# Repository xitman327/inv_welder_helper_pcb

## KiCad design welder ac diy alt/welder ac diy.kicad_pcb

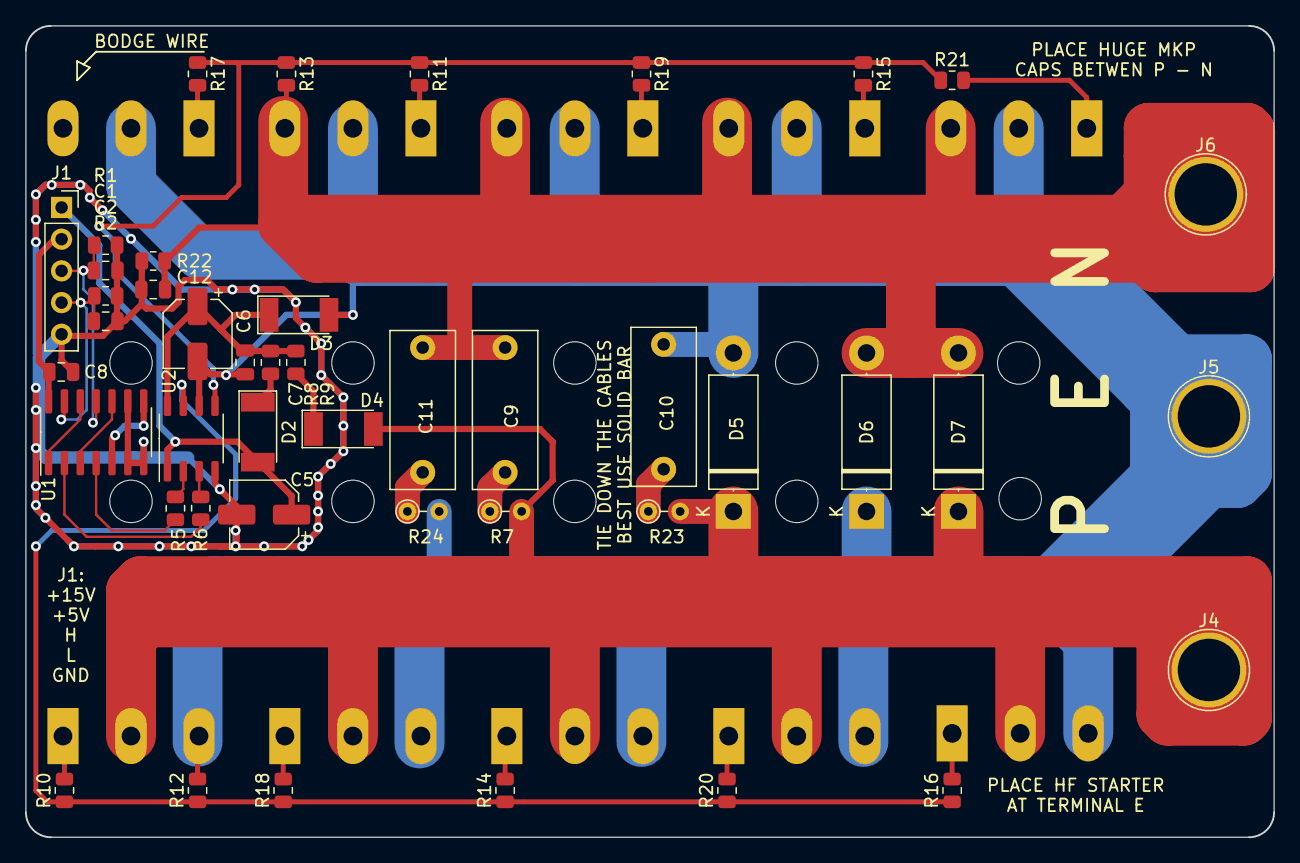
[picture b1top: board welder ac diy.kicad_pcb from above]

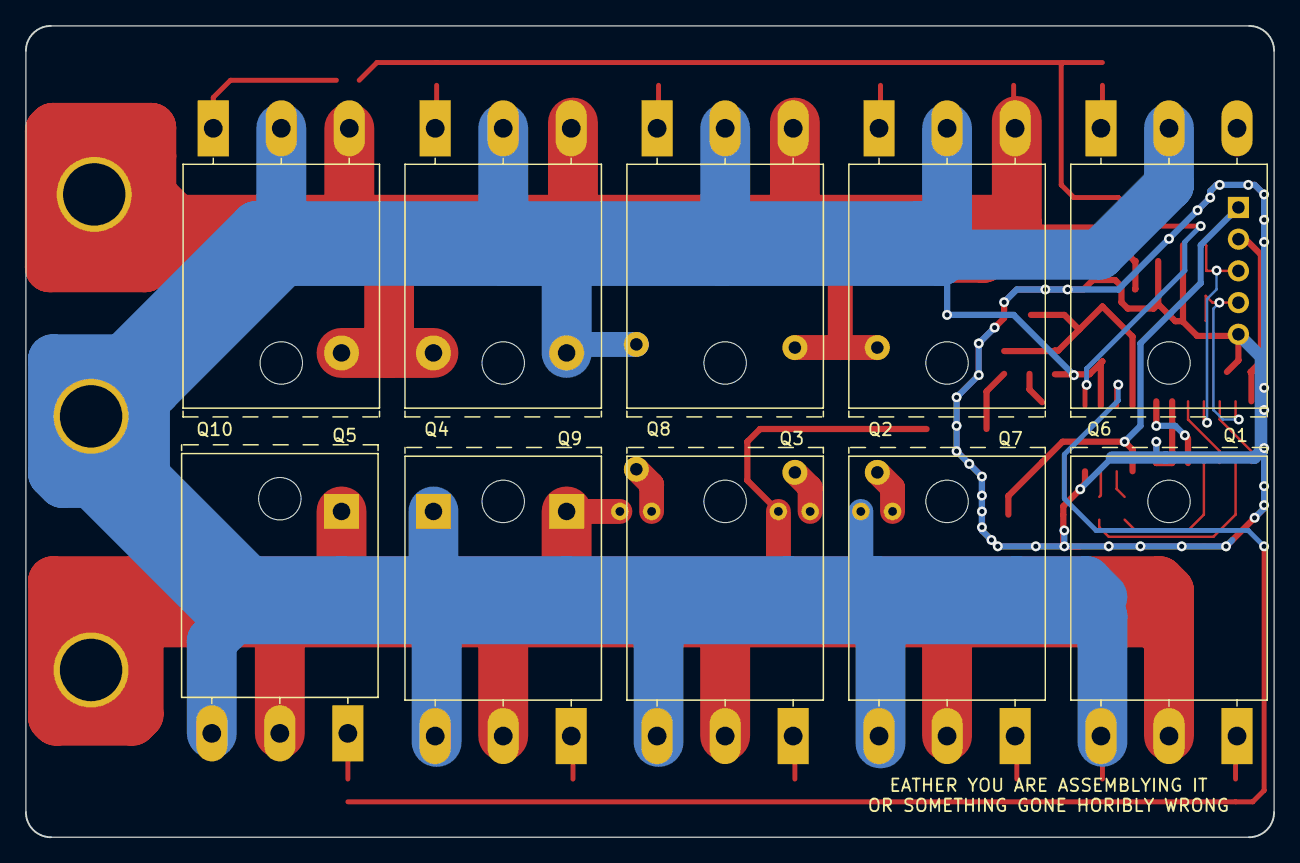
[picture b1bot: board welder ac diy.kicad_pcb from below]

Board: 2 copper layers, 100.0 x 65.0 mm, 54 parts (10 on the bottom side), 33 nets.

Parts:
C1, C2, C7, C8, C12: C_Small; C_0805_2012Metric
C5, C6: C_Polarized_Small; CP_Elec_5x5.7
C9, C10, C11: C_Small; C_Disc_D12.5mm_W5.0mm_P10.00mm
D2, D3, D4: D_Small; D_MELF
D5, D6, D7: D_Small; D_5W_P12.70mm_Horizontal
J1: Conn_01x05; PinSocket_1x05_P2.54mm_Vertical
J4, J5, J6: Conn_01x01; TestPoint_Plated_Hole_D5.0mm
Q1, Q2, Q3, Q4, Q5, Q6, Q7, Q8, Q9, Q10: Q_NMOS_GDS; TO-3P-3_Horizontal_TabUp
R1, R2, R5, R6, R8, R9, R10, R11, R12, R13, R14, R15, R16, R17, R18, R19, R20, R21, R22: R_Small; R_0805_2012Metric
R7, R23, R24: R_Small; R_Axial_DIN0204_L3.6mm_D1.6mm_P2.54mm_Vertical
U1: 74HC04; SO-14_3.9x8.65mm_P1.27mm
U2: IR2101; SOP-8_3.9x4.9mm_P1.27mm

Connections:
+5V: C8.1, J1.2, U1.14 (VCC)
+15V: C5.1, D2.2 (A), J1.1, U2.1 (VCC)
/in+: D4.2 (A), D5.1 (K), D7.1 (K), J4.1, Q1.2 (D), Q3.2 (D), Q5.2 (D), Q7.2 (D), Q9.2 (D), R7.2, R23.2
/in-: C9.2, C11.2, C12.2, D6.2 (A), D7.2 (A), J6.1, Q2.3 (S), Q4.3 (S), Q6.3 (S), Q8.3 (S), Q10.3 (S), R13.2, R22.2
/outP: C6.2, C7.2, C10.2, D3.2 (A), D5.2 (A), D6.1 (K), J5.1, Q1.3 (S), Q2.2 (D), Q3.3 (S), Q4.2 (D), Q5.3 (S), Q6.2 (D), Q7.3 (S), Q8.2 (D), Q9.3 (S), Q10.2 (D), R12.2, R24.2, U2.6 (VS)
GND: C1.2, C2.2, C5.2, C8.2, C12.1, J1.5, R1.1, R2.1, R22.1, U1.6, U1.7 (GND), U1.9, U2.4 (COM)
unnamed: C9.1, R7.1
unnamed: C10.1, R23.1
unnamed: C11.1, R24.1
unnamed: D2.1 (K), R8.1
unnamed: C6.1, C7.1, D3.1 (K), R8.2, R9.1, U2.8 (VB)
unnamed: D4.1 (K), R9.2
unnamed: C1.1, J1.3, R1.2, U1.11
unnamed: C2.1, J1.4, R2.2, U1.13
unnamed: Q1.1 (G), R10.2
unnamed: Q2.1 (G), R11.2
unnamed: Q3.1 (G), R14.2
unnamed: Q4.1 (G), R15.2
unnamed: Q5.1 (G), R16.2
unnamed: Q6.1 (G), R17.2
unnamed: Q7.1 (G), R18.2
unnamed: Q8.1 (G), R19.2
unnamed: Q9.1 (G), R20.2
unnamed: Q10.1 (G), R21.2
unnamed: R5.1, U1.4
unnamed: R6.1, U1.2
unnamed: U1.1, U1.12
unnamed: U1.3, U1.10
unnamed: U1.5, U1.8
unnamed: R5.2, U2.2 (HIN)
unnamed: R10.1, R12.1, R14.1, R16.1, R18.1, R20.1, U2.7 (HO)
unnamed: R6.2, U2.3 (LIN)
unnamed: R11.1, R13.1, R15.1, R17.1, R19.1, R21.1, U2.5 (LO)

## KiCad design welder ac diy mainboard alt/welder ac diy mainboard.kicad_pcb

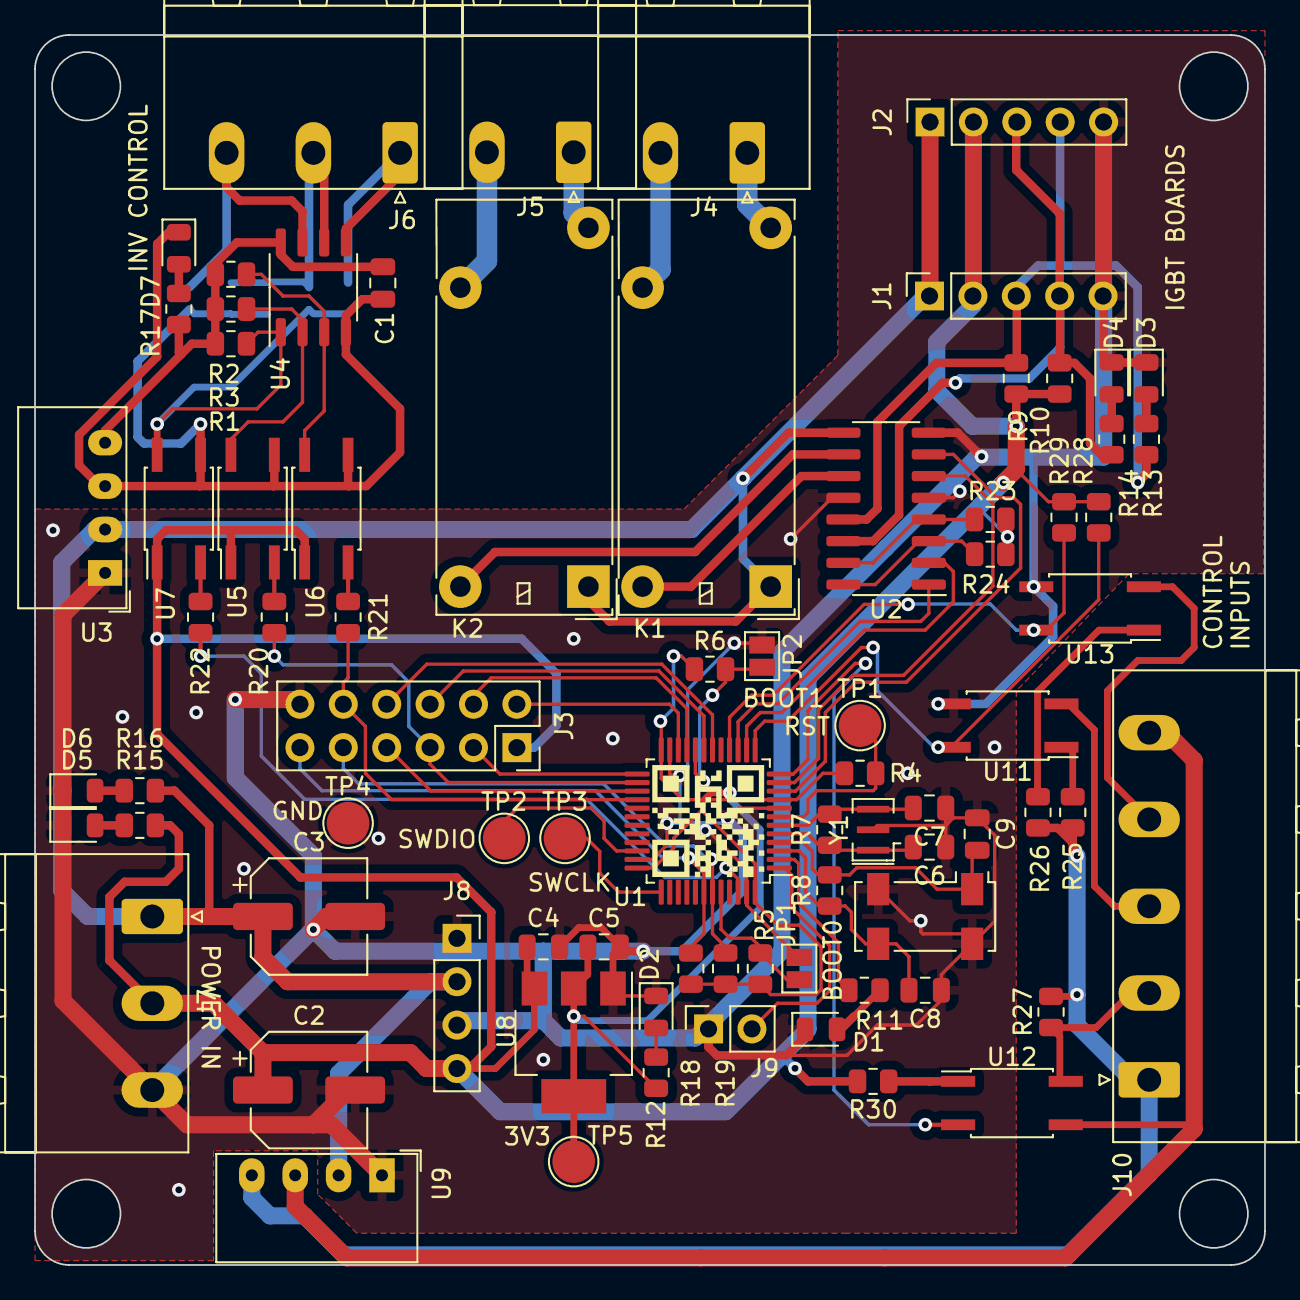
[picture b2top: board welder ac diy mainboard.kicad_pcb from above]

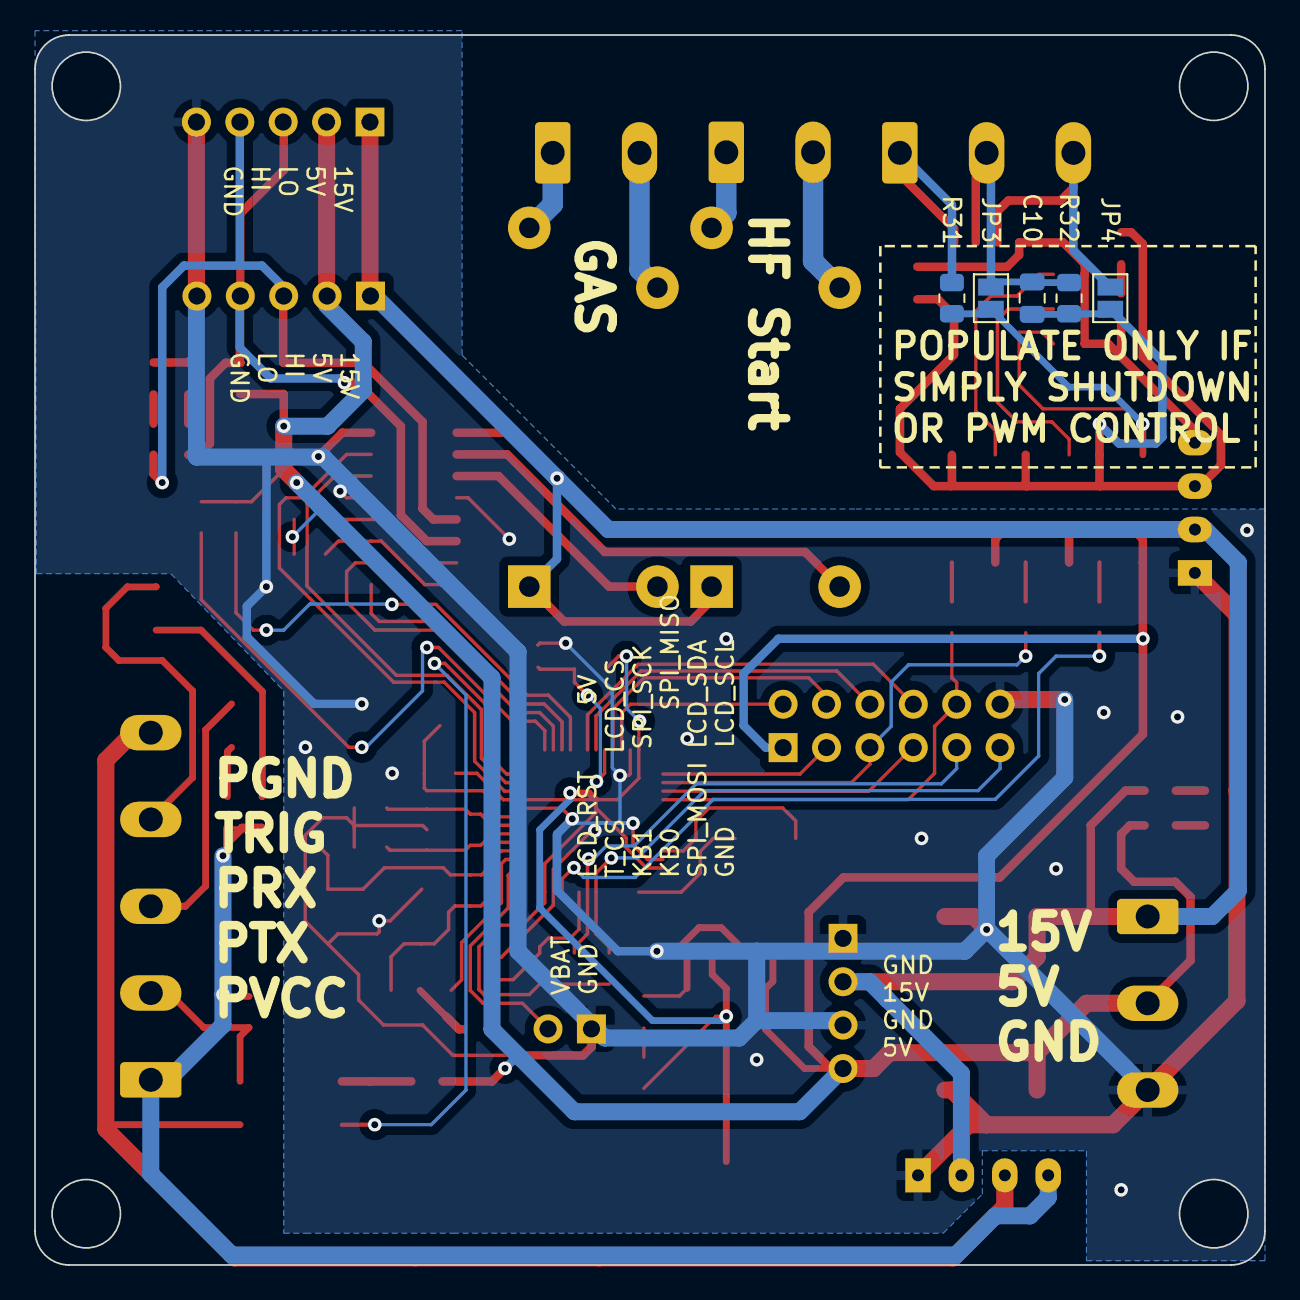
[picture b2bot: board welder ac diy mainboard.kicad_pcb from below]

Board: 2 copper layers, 72.0 x 72.0 mm, 84 parts (5 on the bottom side), 69 nets.

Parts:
C1, C4, C5, C6, C7, C8, C9, C10: C_Small; C_0805_2012Metric
C2, C3: C_Polarized_Small; CP_Elec_6.3x3
D1, D2, D3, D4, D5, D6, D7: LED; LED_0805_2012Metric
J1, J2: Conn_01x05; PinSocket_1x05_P2.54mm_Vertical
J3: Conn_02x06_Odd_Even; PinSocket_2x06_P2.54mm_Vertical
J4, J5: Conn_01x02; PhoenixContact_MSTBA_2,5_2-G-5,08_1x02_P5.08mm_Horizontal
J6, J7: Conn_01x03; PhoenixContact_MSTBA_2,5_3-G-5,08_1x03_P5.08mm_Horizontal
J8: Conn_01x04; PinSocket_1x04_P2.54mm_Vertical
J9: Conn_01x02; PinSocket_1x02_P2.54mm_Vertical
J10: Conn_01x05; PhoenixContact_MSTBA_2,5_5-G-5,08_1x05_P5.08mm_Horizontal
JP1, JP2, JP3, JP4: SolderJumper_2_Open; SolderJumper-2_P1.3mm_Open_Pad1.0x1.5mm
K1, K2: ADW11; Relay_1P1T_NO_10x24x18.8mm_Panasonic_ADW11xxxxW_THT
R1, R2, R3, R4, R5, R6, R7, R8, R9, R10, R11, R12, R13, R14, R15, R16, R17, R18, R19, R20, R21, R22, R23, R24, R25, R26, R27, R28, R29, R30, R31, R32: R_Small; R_0805_2012Metric
TP1, TP2, TP3, TP4, TP5: TestPoint; TestPoint_Pad_D2.5mm
U1: STM32F103C8Tx; LQFP-48_7x7mm_P0.5mm
U2: ULN2003; SOP-16_3.9x9.9mm_P1.27mm
U3, U9: CRE1S0515SC; Converter_DCDC_Murata_CRE1xxxxxxSC_THT
U4: MCP41010; SOP-8_3.9x4.9mm_P1.27mm
U5, U6, U7, U11, U12, U13: LTV-357T; SO-4_4.4x3.6mm_P2.54mm
U8: AMS1117-2.85; SOT-223-3_TabPin2
Y1: Crystal_GND2_Small; Resonator_SMD_Murata_CSTxExxV-3Pin_3.0x1.1mm
Y3: Crystal_GND24_Small; Crystal_SMD_Abracon_ABS25-4Pin_8.0x3.8mm

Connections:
+5V: C2.1, C4.1, J1.2, J2.2, J3.1, J7.2, J8.4, R9.1, R10.1, R15.1, R23.1, R24.1, R28.2, R29.2, R30.2, U5.1, U6.1, U7.1, U8.3 (VI)
+15V: C3.1, J1.1, J2.1, J7.1, J8.2, K1.1, K2.1, R16.1, U2.9 (COM), U3.2 (+VIN), U9.2 (+VIN)
/CLK1: R24.2, U2.3 (I3), U2.16 (O1)
/CLK2: J1.4, J2.3, R10.2, R14.1, U2.14 (O3)
/CLK_: U1.15 (PA5), U2.1 (I1)
/EN1: R23.2, U2.4 (I4), U2.15 (O2)
/EN2: J1.3, J2.4, R9.2, R13.1, U2.13 (O4)
/EN_: U1.14 (PA4), U2.2 (I2)
/GAS_: U1.11 (PA1), U2.6 (I6)
/HF_: U1.10 (PA0), U2.7 (I7)
/KB0: J3.8, U1.18 (PB0)
/KB1: J3.6, U1.19 (PB1)
/LCD_CS: J3.3, U1.25 (PB12)
/LCD_RST: J3.2, U1.22 (PB11)
/LCD_SCL: J3.11, R18.2, U1.42 (PB6)
/LCD_SDA: J3.9, R19.2, U1.43 (PB7)
/LED: R11.1, U1.2 (PC13)
/PED_GND: J10.5, U9.3 (-VOUT), U12.3
/PED_RX: J10.3, U11.2
/PED_RX_: R28.1, U1.13 (PA3), U11.4
/PED_TX: J10.2, R27.1, U12.4
/PED_TX_: U1.12 (PA2), U12.2
/PED_VCC: J10.1, R25.2, R26.2, R27.2, U9.4 (+VOUT)
/POT_CS: R22.1, U1.46 (PB9)
/SPI_MISO: J3.7, U1.27 (PB14)
/SPI_MOSI: J3.10, R21.1, U1.28 (PB15)
/SPI_SCK: J3.5, R20.1, U1.26 (PB13)
/TR0: R29.1, U1.16 (PA6), U13.4
/TRIG_EX: J10.4, U13.2
/T_CS: J3.4, U1.21 (PB10)
GND: C2.2, C3.2, C4.2, C5.2, C6.1, C7.1, C8.1, C9.1, D1.1 (K), D2.1 (K), D3.1 (K), D4.1 (K), D5.1 (K), D6.1 (K), J1.5, J2.5, J3.12, J7.3, J8.1, J8.3, J9.1, JP1.1 (A), JP2.1 (A), TP4.1, U1.8 (VSSA), U1.23 (VSS), U1.35 (VSS), U1.47 (VSS), U2.5 (I5), U2.8 (GND), U2.12 (O5), U3.1 (-VIN), U8.1 (GND), U9.1 (-VIN), U11.3, U13.3, Y1.2, Y3.2, Y3.4
unnamed: D1.2 (A), R11.2
unnamed: D2.2 (A), R12.2
unnamed: D3.2 (A), R13.2
unnamed: D4.2 (A), R14.2
unnamed: D5.2 (A), R15.2
unnamed: D6.2 (A), R16.2
unnamed: D7.2 (A), R17.2
unnamed: C1.2, C10.1, D7.1 (K), JP4.1 (A), R32.1, U3.3 (-VOUT), U4.4 (VSS), U5.3, U6.3, U7.3
unnamed: J4.1, K1.3
unnamed: J4.2, K1.5
unnamed: J5.1, K2.3
unnamed: J5.2, K2.5
unnamed: J6.1, R31.2, U4.5 (PA0)
unnamed: C10.2, J6.2, JP3.2 (B), R32.2, U4.6 (PW0)
unnamed: J6.3, JP4.2 (B), U4.7 (PB0)
unnamed: J9.2, U1.1 (VBAT)
unnamed: JP1.2 (B), R5.2, U1.44 (BOOT0)
unnamed: JP2.2 (B), R6.2, U1.20 (PB2)
unnamed: R20.2, U5.2
unnamed: R21.2, U6.2
unnamed: R22.2, U7.2
unnamed: R25.1, U11.1
unnamed: R26.1, U13.1
unnamed: R30.1, U12.1
unnamed: R4.2, TP1.1, U1.7 (NRST)
unnamed: TP2.1, U1.34 (PA13)
unnamed: TP3.1, U1.37 (PA14)
unnamed: C8.2, R8.1, U1.3 (PC14), Y3.3
unnamed: C9.2, R8.2, U1.4 (PC15), Y3.1
unnamed: C6.2, R7.1, U1.5 (PD0), Y1.1
unnamed: C7.2, R7.2, U1.6 (PD1), Y1.3
unnamed: C5.1, R4.1, R5.1, R6.1, R12.1, R18.1, R19.1, TP5.1, U1.9 (VDDA), U1.24 (VDD), U1.36 (VDD), U1.48 (VDD), U8.2 (VO)
unnamed: K1.6, U2.11 (O6)
unnamed: K2.6, U2.10 (O7)
unnamed: C1.1, R1.1, R2.1, R3.1, R17.1, U3.4 (+VOUT), U4.8 (VDD)
unnamed: R3.2, U4.2 (SCK), U5.4
unnamed: R2.2, U4.3 (SI), U6.4
unnamed: JP3.1 (A), R1.2, R31.1, U4.1 (~CS), U7.4
